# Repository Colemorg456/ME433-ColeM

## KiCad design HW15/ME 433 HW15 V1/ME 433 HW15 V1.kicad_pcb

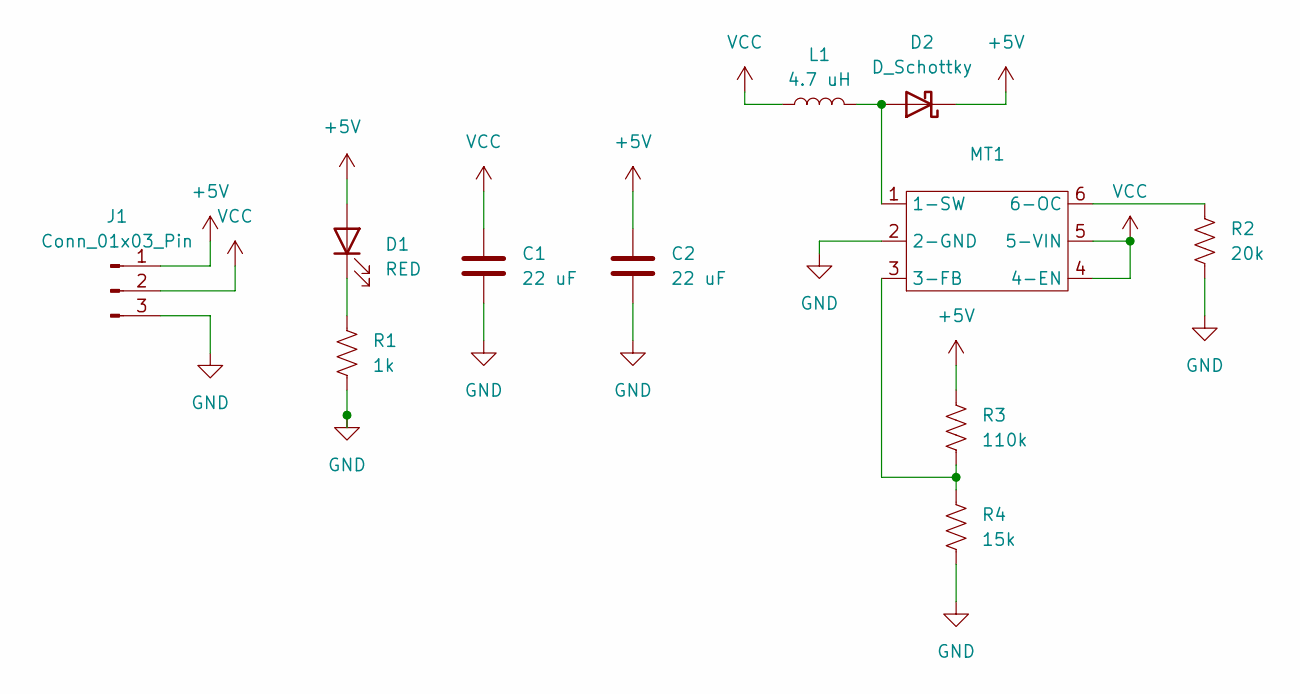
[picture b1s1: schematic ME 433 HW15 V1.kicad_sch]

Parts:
C1, C2: 22 uF; CP_Radial_D5.0mm_P2.00mm
D1: RED; LED_0603_1608Metric_Pad1.05x0.95mm_HandSolder
D2: D_Schottky; D_SOD-123
J1: Conn_01x03_Pin; PinSocket_1x03_P2.54mm_Vertical
L1: 4.7 uH; L_0805_2012Metric
MT1: SOT-23-6
R1: 1k; R_0815_2038Metric_Pad1.20x4.05mm_HandSolder
R2: 20k; R_0815_2038Metric_Pad1.20x4.05mm_HandSolder
R3: 110k; R_0815_2038Metric_Pad1.20x4.05mm_HandSolder
R4: 15k; R_0815_2038Metric_Pad1.20x4.05mm_HandSolder

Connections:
+5V: C2.1, D1.2 (A), D2.1 (K), J1.1, R3.1
GND: C1.2, C2.2, J1.3, MT1.2 (2-GND), R1.2, R2.2, R4.2
unnamed: D1.1 (K), R1.1
unnamed: D2.2 (A), L1.2, MT1.1 (1-SW)
unnamed: MT1.3 (3-FB), R3.2, R4.1
unnamed: MT1.6 (6-OC), R2.1
VCC: C1.1, J1.2, L1.1, MT1.4 (4-EN), MT1.5 (5-VIN)

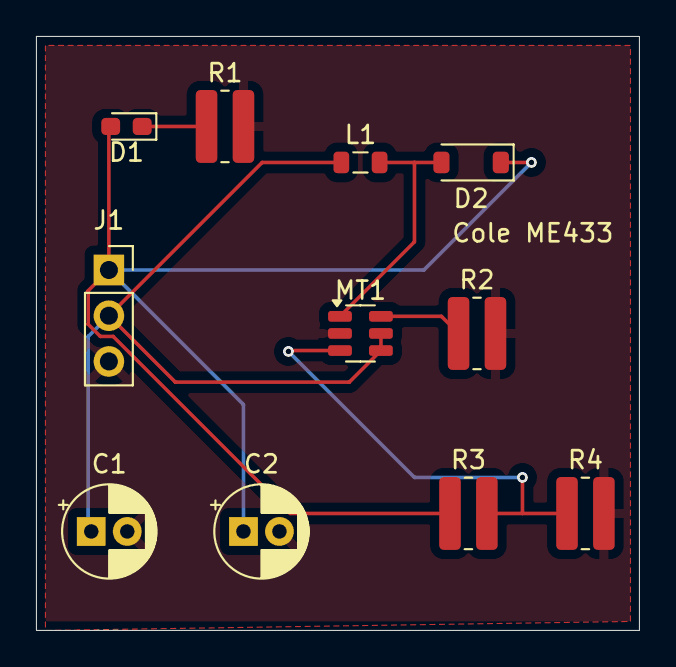
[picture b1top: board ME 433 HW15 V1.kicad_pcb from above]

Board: 2 copper layers, 33.5 x 33.0 mm, 11 parts (0 on the bottom side), 7 nets.

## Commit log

2025-04-10 HW2
    HW2 assignment that makes the LED blink every time you press the button
2025-04-10 HW3 Initial Code
    Testing the potentiometer ADC reader
2025-04-11 HW3
    Final HW3 code
2025-04-22 HW4 Initial
    This is displaying 1.64 V on the oscilloscope for the SPI chip
2025-04-22 Final code
    This more or less is gettign the tiranlge and sin wave to work
2025-04-22 Add files via upload
    Scope outputs for the DAC
2025-04-28 Math and timing with serial
    for HW5
2025-04-28 initializing PSI RAM functions
    Making 3 functions, one to initilize sequence mode, one to activate and write to the RAM chip, one to activate and read from the ram chip. Lots of bitshifting involved
2025-04-28 scope trace
2025-04-29 HW6 I2C with MCP23008
    Full homework
2025-04-29 Demo video for I2C DIp Chip
2025-05-08 HW 7 Beginning
    Just initializing the OLED screen
2025-05-08 HW7 OLED basic function
    Basic OLED functioning now
2025-05-08 HW7 with ADC
    Writing to the OLED with the Potentionmeter ADC
2025-05-08 Video of ADC
2025-05-09 HW8 PWM and RBG
    Got the servo working
2025-05-09 HW8 with LED and servo both running
    it looks very pretty
2025-05-09 Add files via upload
    Hard to see lights changing on the video due to camera lense
2025-05-09 HW9 Multicore
    Got the multicore working with the LED and ADC
2025-05-09 Video of code
2025-05-12 HW10 part 4
    getting started on signal processing by generating plots using fourier transform
2025-05-12 Part5 of HW10
    Moving average section with images
2025-05-12 HW10 Part6
2025-05-12 Part7 of HW10
2025-05-17 HW11 Moving the Mouse
    My PICO enumerates as a USB and I can control the mouse with 2 potentiometers or set it to idle in a circle
2025-05-17 Demo Video For Mouse
2025-05-21 HW13 IMU with OLED Screen
2025-05-28 HW 12
    Got the camera wired up and working
2025-05-29 HW 16 Motor Control
    PWM for both motors simulatanteously, moving up and down when pressing + or - in screen
2025-05-30 Wheel turn fix
    Making it so both wheels go forward or backward in unison
2025-05-31 HW15 PCB design
    Full schematic and board rendering and gerber export for PCB designing
2025-05-31 Adding photos of PCB
2025-05-31 Assembling the robot code
    Starting to put together the code that will be loaded on to my robot, so far I have the OLED screen working
2025-06-01 HW 17 motor controller basics
    Basics of motor controller except I dont have the input for the camera. Using the OLED screen to see the duty cycle instead of two LEDs
2025-06-01 HW12 Camera
    Uploading new camera code
2025-06-01 Updated Robot Code
    My most recent update to the line following robot code. Right now My heartbeat LED is working and my OLED screen is updating to show me how the camera is working, I need to test the camera on the rac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
2025-06-02 HW17 testing camera
    Testing camera and recording video to show accuracy of line following
2025-06-02 Added PD controller
    Messing with the gains, robot can do basic line following but cant do the sharp turns at all
2025-06-03 Editing and Calibrating
2025-06-05 Final Calibrations for line-following accuracy
2025-09-24 ME 333 Motor Project Code
